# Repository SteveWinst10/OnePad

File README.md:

# OnePad
OnePad is a macropad named after One Piece :) . It has 8 keys , a rotary encoder , an 0.91 inch oled display and 8 LEDs . It uses the KMK firmware.

## BOM:
 - 1x XIAO RP2040
 - 8x Cherry MX switches
 - 1x EC11 Rotary Encoder
 - 1x 128x32 OLED Display
 - 8x SK6812 MINI-E LEDs
 - 9x 1N4148 Diodes
 - 8x DSA keycaps
 - 4x M3x16 Bolt
 - 4x M3 Heatset
  
## Firmware
It uses KMK firmware. The keys are used for media key functionality and other macros for my WM. Rotary encoder will be used for volume.

|  Schematic | PCB  | Case  |
| :------------ | :------------ | :------------ |
| |  | |

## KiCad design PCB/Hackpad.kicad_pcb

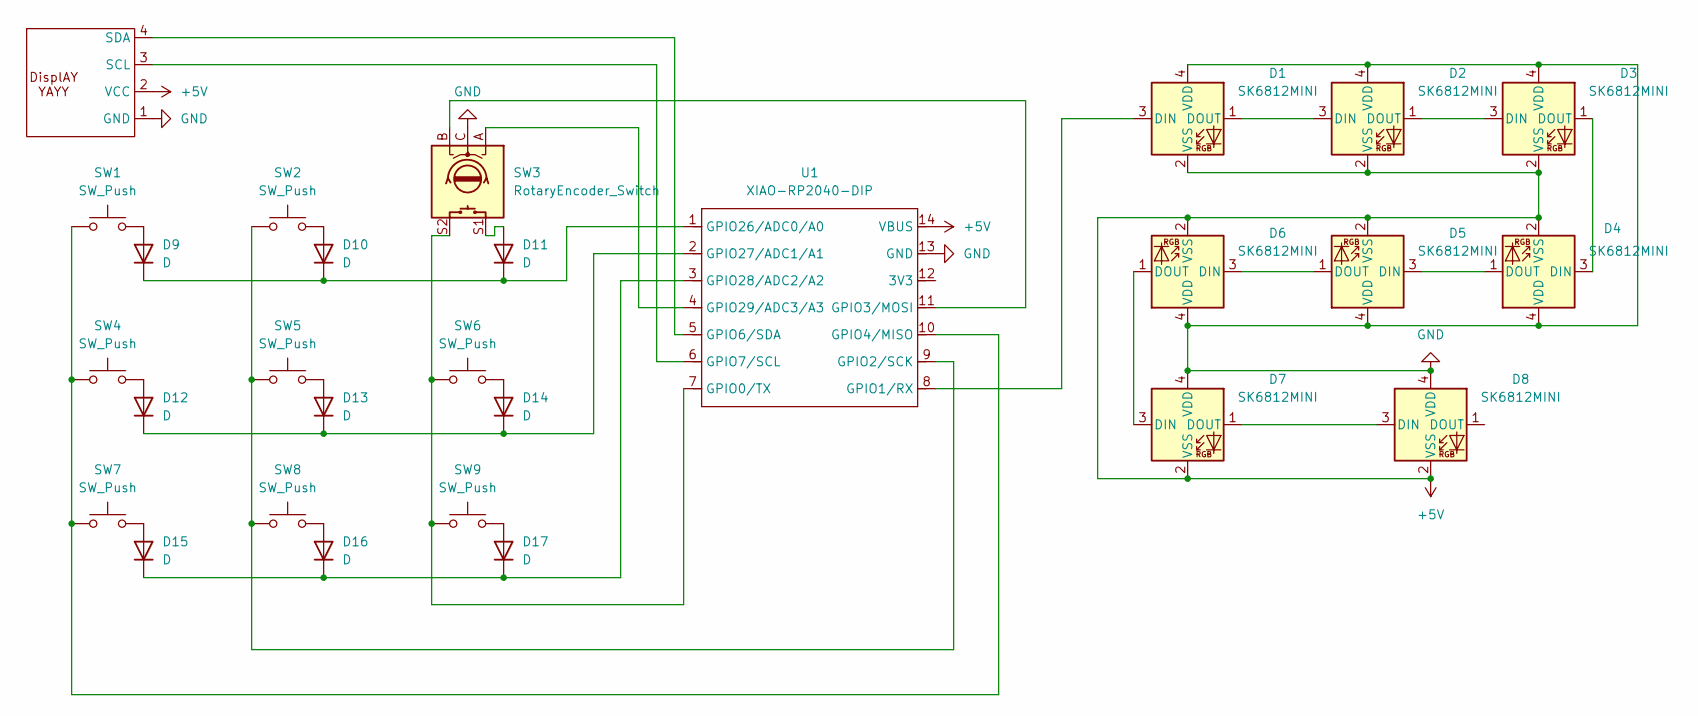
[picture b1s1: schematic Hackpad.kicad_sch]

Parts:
D1, D2, D3, D4, D5, D6, D7, D8: SK6812MINI; LED_SK6812MINI_PLCC4_3.5x3.5mm_P1.75mm
D9, D10, D11, D12, D13, D14, D15, D16, D17: D; D_DO-35_SOD27_P7.62mm_Horizontal
SW1, SW2, SW4, SW5, SW6, SW7, SW8, SW9: SW_Push; SW_Cherry_MX_1.00u_PCB
SW3: RotaryEncoder_Switch; RotaryEncoder_Alps_EC11E-Switch_Vertical_H20mm_CircularMoun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
U1: XIAO-RP2040-DIP
U2: SSD1306-0.91-OLED-4pin-128x32

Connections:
+5V: D1.2 (VSS), D2.2 (VSS), D3.2 (VSS), D4.2 (VSS), D5.2 (VSS), D6.2 (VSS), D7.2 (VSS), D8.2 (VSS), U1.14 (VBUS), U2.2 (VCC)
GND: D1.4 (VDD), D2.4 (VDD), D3.4 (VDD), D4.4 (VDD), D5.4 (VDD), D6.4 (VDD), D7.4 (VDD), D8.4 (VDD), SW3.C, U1.13 (GND), U2.1 (GND)
unnamed: D1.3 (DIN), U1.8 (GPIO1/RX)
unnamed: D1.1 (DOUT), D2.3 (DIN)
unnamed: D2.1 (DOUT), D3.3 (DIN)
unnamed: D3.1 (DOUT), D4.3 (DIN)
unnamed: D4.1 (DOUT), D5.3 (DIN)
unnamed: D5.1 (DOUT), D6.3 (DIN)
unnamed: D6.1 (DOUT), D7.3 (DIN)
unnamed: D7.1 (DOUT), D8.3 (DIN)
unnamed: D9.2 (A), SW1.2
unnamed: D10.2 (A), SW2.2
unnamed: D9.1 (K), D10.1 (K), D11.1 (K), U1.1 (GPIO26/ADC0/A0)
unnamed: D11.2 (A), SW3.S1
unnamed: D12.2 (A), SW4.2
unnamed: D12.1 (K), D13.1 (K), D14.1 (K), U1.2 (GPIO27/ADC1/A1)
unnamed: D13.2 (A), SW5.2
unnamed: D14.2 (A), SW6.2
unnamed: D15.2 (A), SW7.2
unnamed: D15.1 (K), D16.1 (K), D17.1 (K), U1.3 (GPIO28/ADC2/A2)
unnamed: D16.2 (A), SW8.2
unnamed: D17.2 (A), SW9.2
unnamed: SW3.S2, SW6.1, SW9.1, U1.7 (GPIO0/TX)
unnamed: SW2.1, SW5.1, SW8.1, U1.9 (GPIO2/SCK)
unnamed: SW3.B, U1.11 (GPIO3/MOSI)
unnamed: SW1.1, SW4.1, SW7.1, U1.10 (GPIO4/MISO)
unnamed: U1.5 (GPIO6/SDA), U2.4 (SDA)
unnamed: U1.6 (GPIO7/SCL), U2.3 (SCL)
unnamed: SW3.A, U1.4 (GPIO29/ADC3/A3)

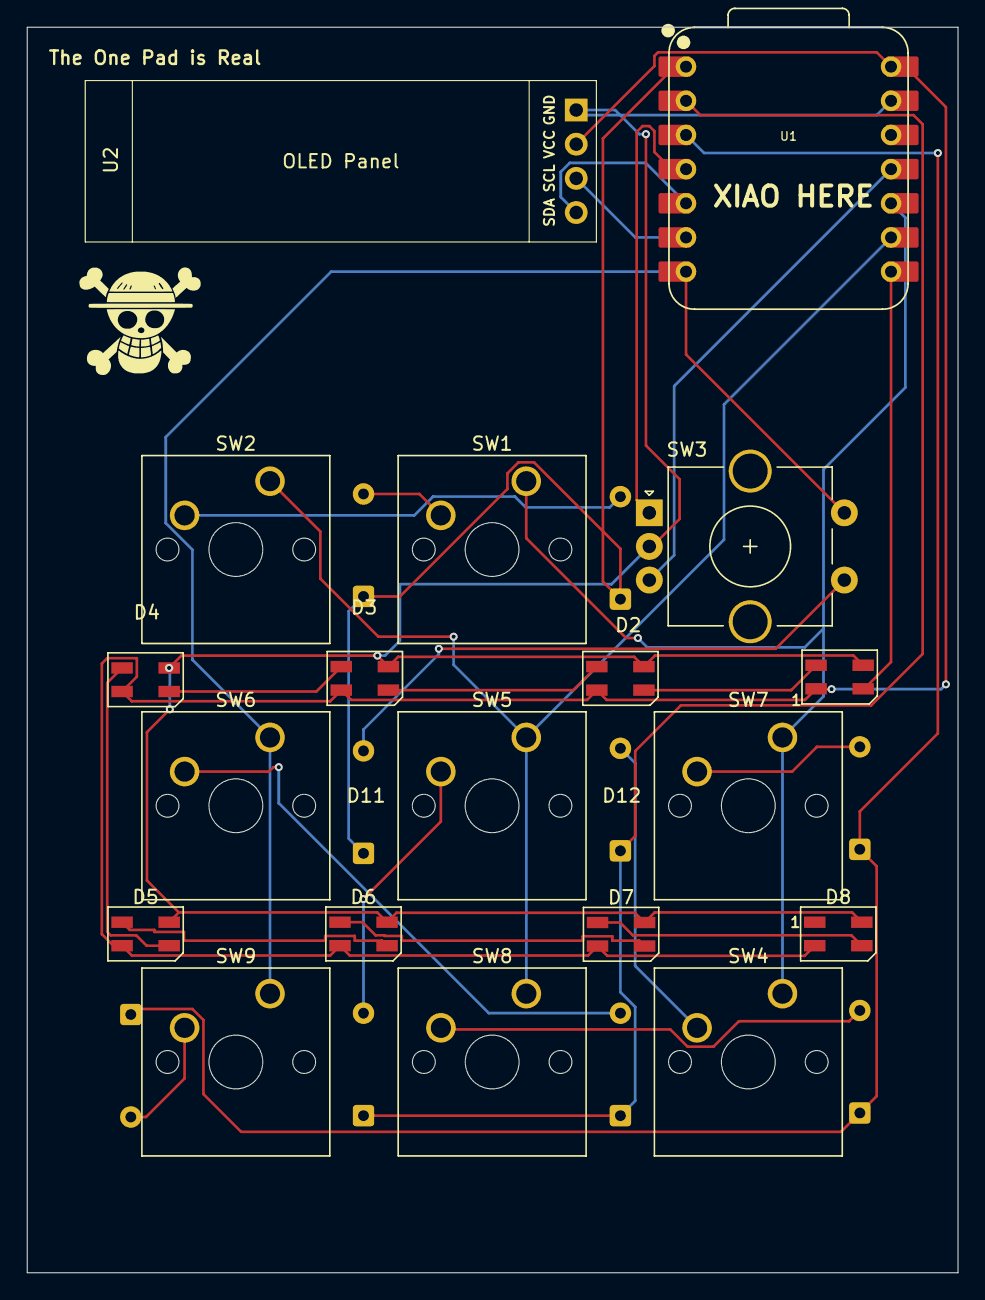
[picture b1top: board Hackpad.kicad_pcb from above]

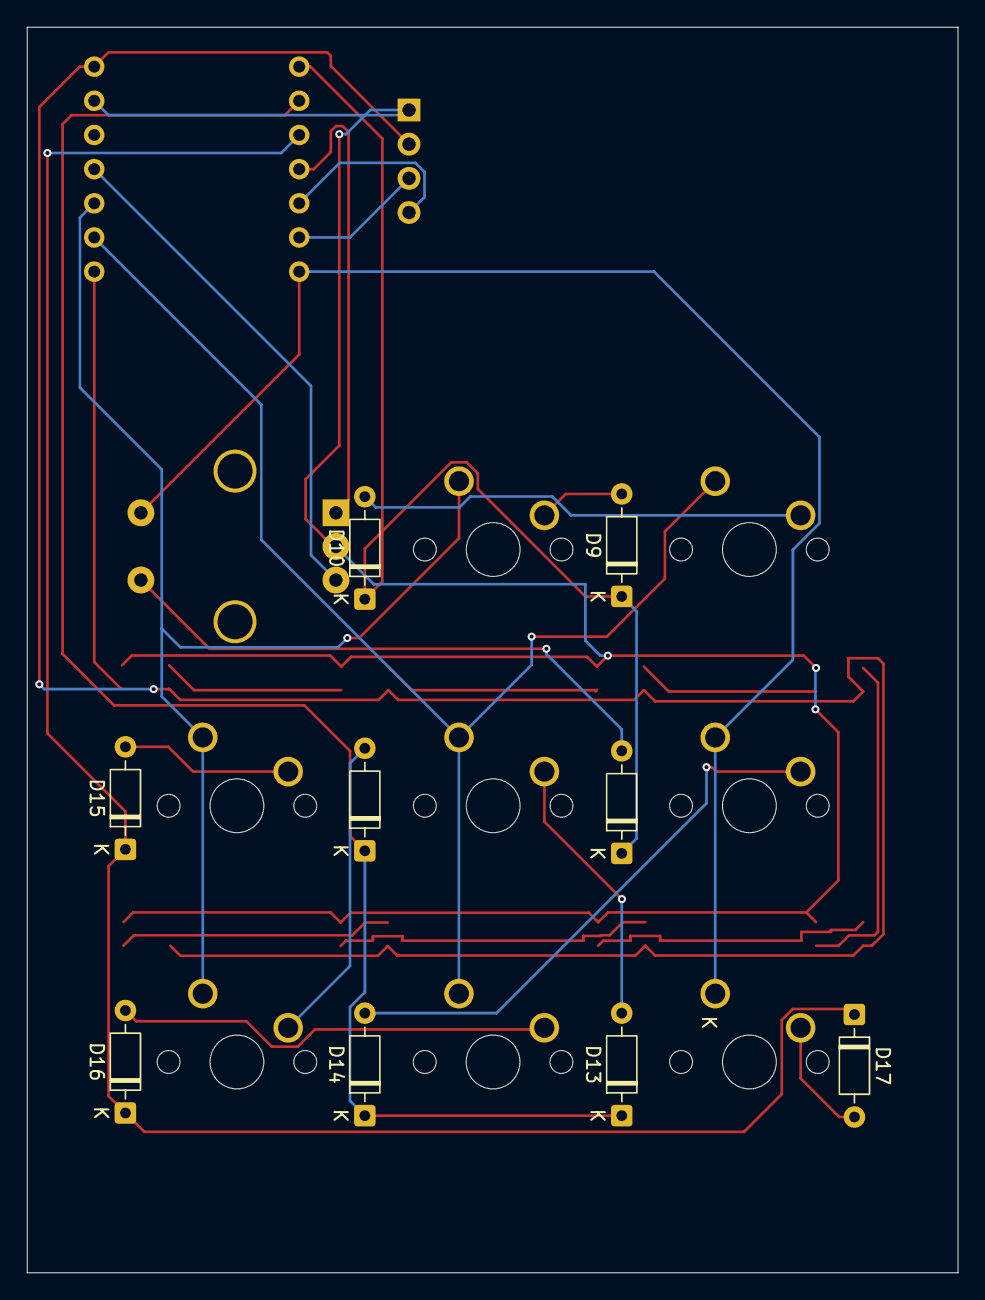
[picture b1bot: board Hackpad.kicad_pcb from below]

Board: 2 copper layers, 69.2 x 92.6 mm, 28 parts (9 on the bottom side), 29 nets.

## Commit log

2025-08-05 fixed missing body
